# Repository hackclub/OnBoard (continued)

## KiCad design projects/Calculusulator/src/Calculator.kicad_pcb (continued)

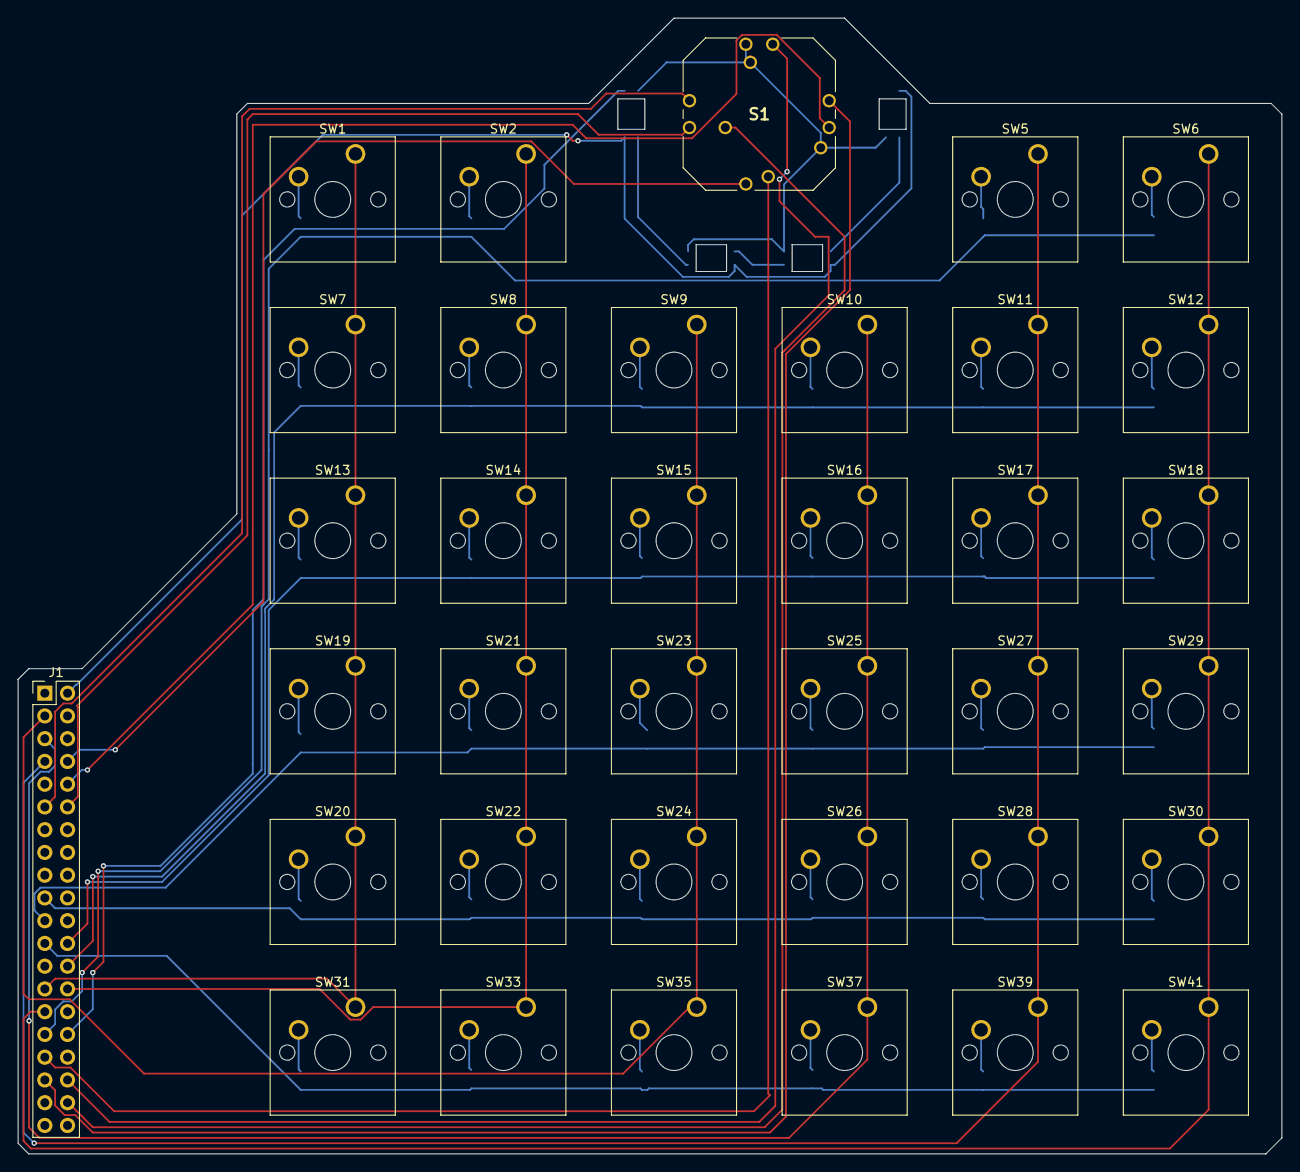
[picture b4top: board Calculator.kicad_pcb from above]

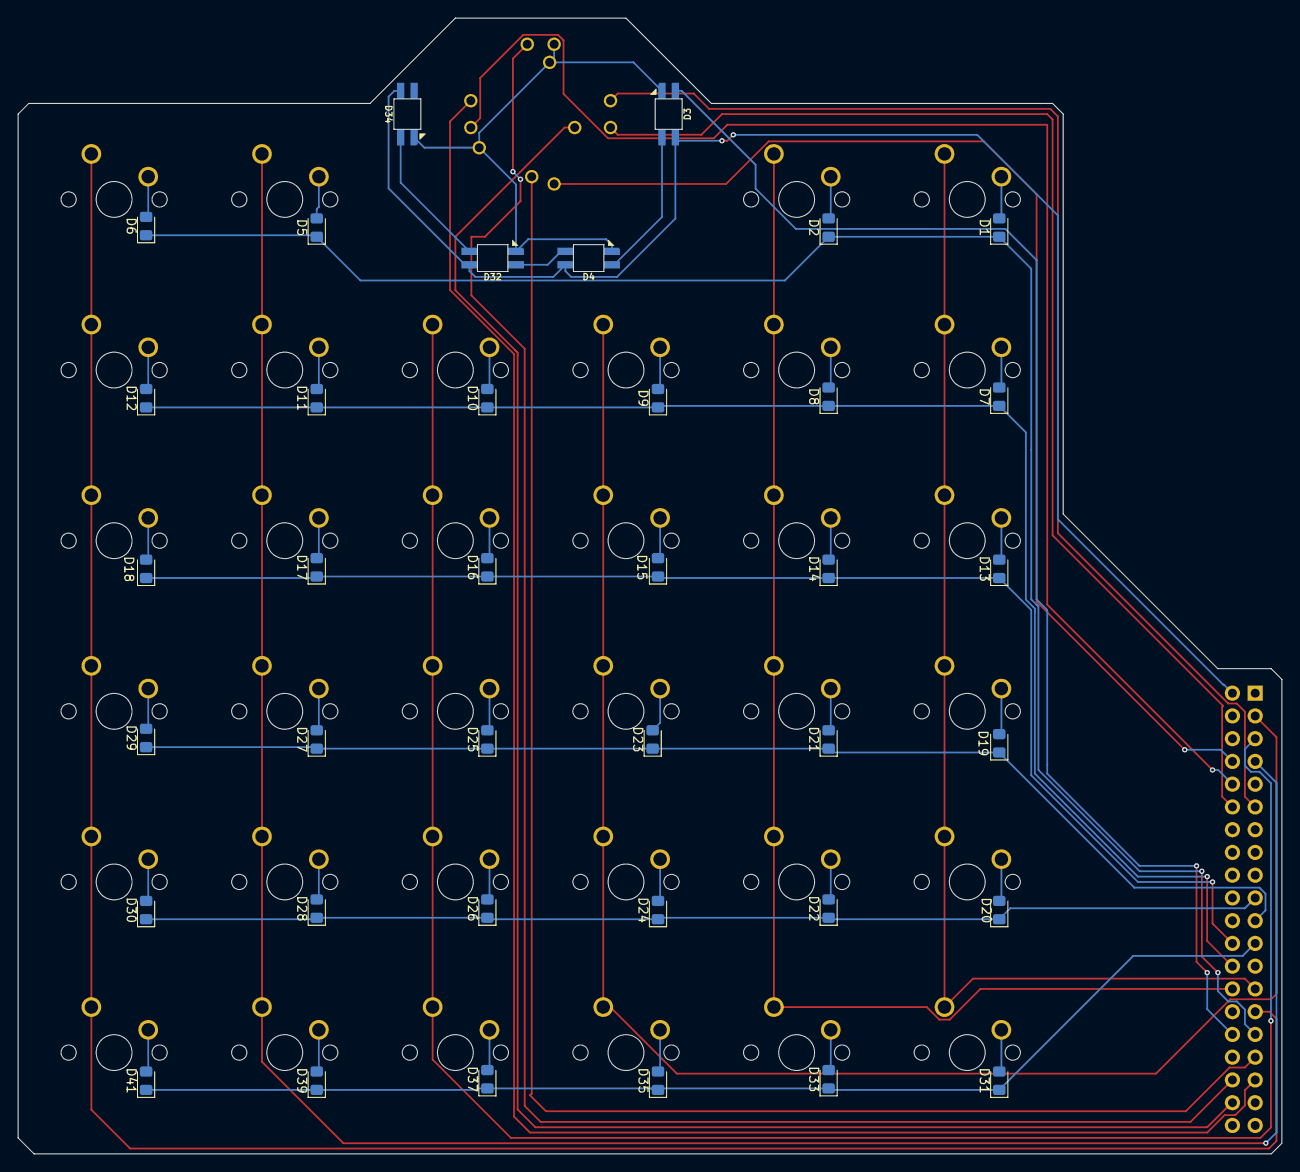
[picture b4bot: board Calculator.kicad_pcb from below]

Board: 2 copper layers, 141.1 x 126.8 mm, 74 parts (38 on the bottom side), 62 nets.

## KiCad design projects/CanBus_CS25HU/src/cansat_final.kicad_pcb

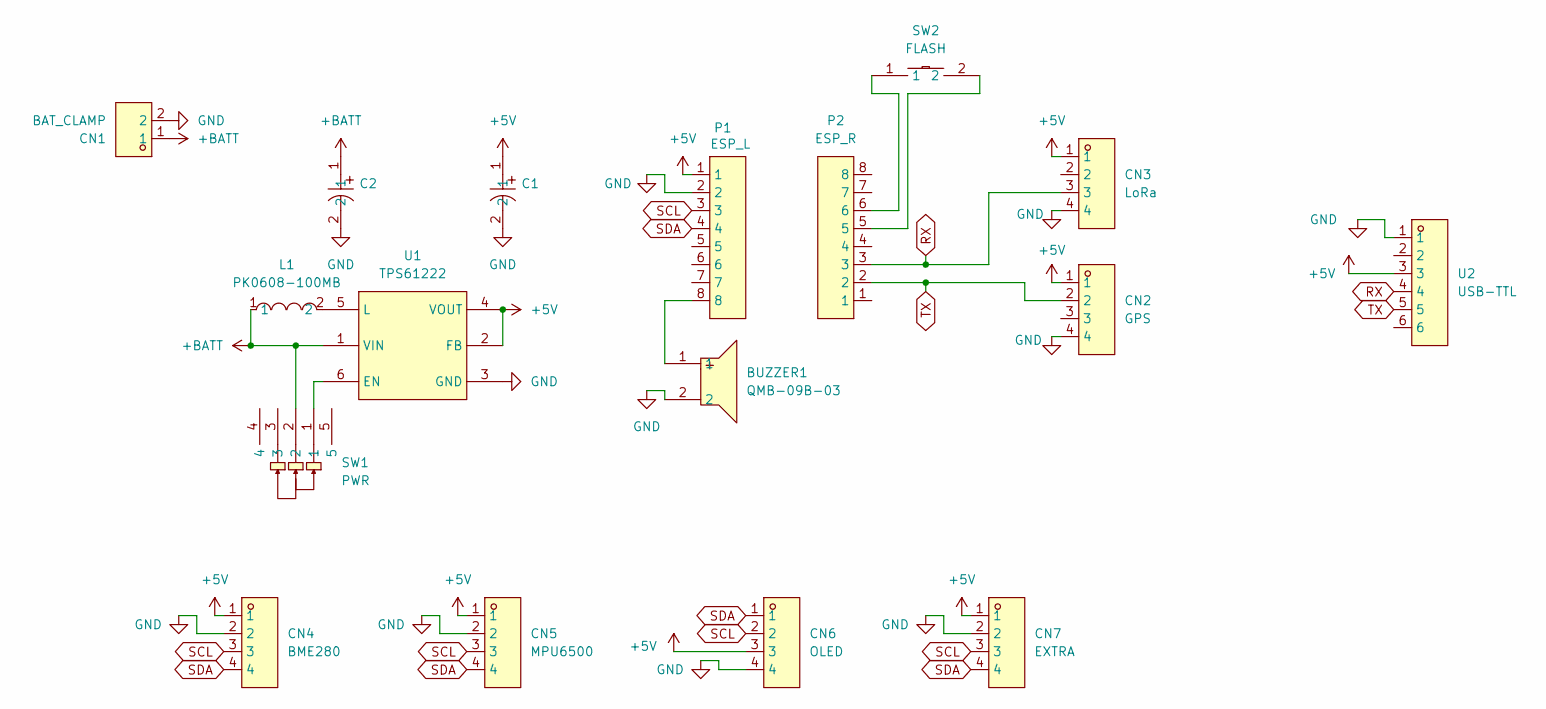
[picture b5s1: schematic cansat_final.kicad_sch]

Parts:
BUZZER1: QMB-09B-03; BUZ-TH_BD9.0-P4.00-D0.6-FD; LCSC Part C96256
C1, C2: 10uF; CAP-TH_BD5.0-P2.00-D0.5-FD-1; LCSC Part C2840034
CN1: BAT_CLAMP; CONN-SMD_2P-P4.00_HDGC4001SMD-S-2P; LCSC Part C5197184
CN2: GPS; CONN-TH_XH-4A; LCSC Part C722867
CN3: LoRa; CONN-TH_XH-4A; LCSC Part C722867
CN4: BME280; CONN-TH_XH-4A; LCSC Part C722867
CN5: MPU6500; CONN-TH_XH-4A; LCSC Part C722867
CN6: OLED; CONN-TH_XH-4A; LCSC Part C722867
CN7: EXTRA; CONN-TH_XH-4A; LCSC Part C722867
L1: PK0608-100MB; IND-TH_BD7.0-P2.50-D0.7; LCSC Part C400296
P1: ESP_L; HDR-TH_8P-P2.54-V-F-1; LCSC Part C27438
P2: ESP_R; HDR-TH_8P-P2.54-V-F-1; LCSC Part C27438
SW1: PWR; SW-TH_SK12D07VG3; LCSC Part C431547
SW2: FLASH; SW-SMD_L6.0-W3.3-LS8.0; LCSC Part C318938
U1: TPS61222; SC-70-6_L2.2-W1.3-P0.65-LS2.1-BR; LCSC Part C116461
U2: USB-TTL; HDR-TH_6P-P2.54-V-F; LCSC Part C7509518

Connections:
+5V: C1.1, CN2.1, CN3.1, CN4.1, CN5.1, CN6.3, CN7.1, P1.1, U1.2 (FB), U1.4 (VOUT), U2.3
+BATT: C2.1, CN1.1, L1.1, SW1.2, U1.1 (VIN)
GND: BUZZER1.2, C1.2, C2.2, CN1.2, CN2.4, CN3.4, CN4.2, CN5.2, CN6.4, CN7.2, P1.2, U1.3 (GND), U2.1
unnamed: BUZZER1.1, P1.8
unnamed: P2.5, SW2.2
unnamed: P2.6, SW2.1
unnamed: SW1.1, U1.6 (EN)
unnamed: L1.2, U1.5 (L)
RX: CN3.3, P2.3, U2.4
SCL: CN4.3, CN5.3, CN6.2, CN7.3, P1.3
SDA: CN4.4, CN5.4, CN6.1, CN7.4, P1.4
TX: CN2.2, P2.2, U2.5

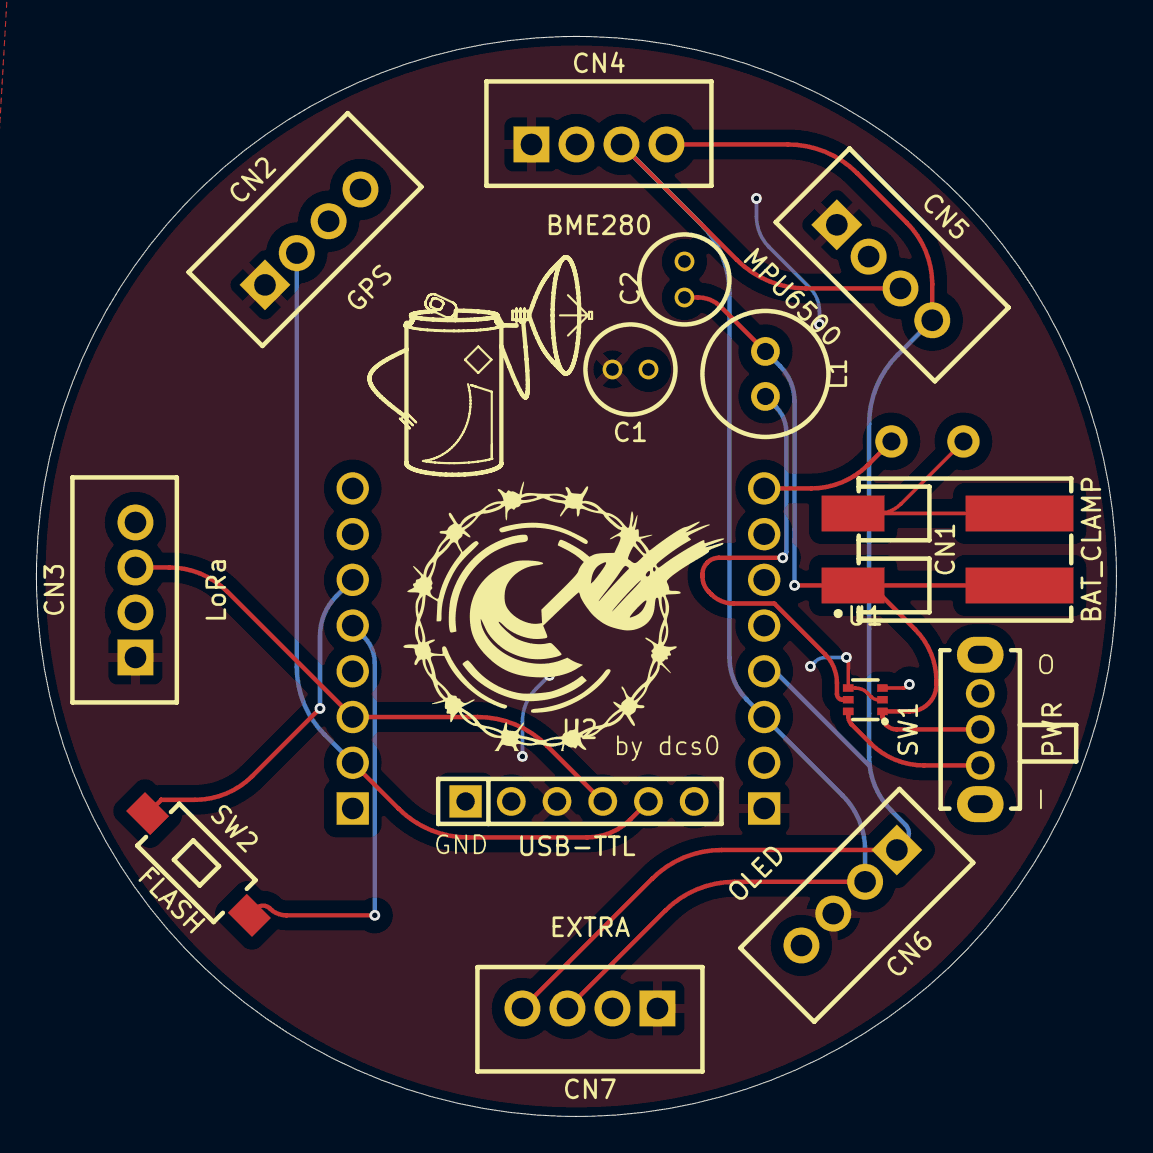
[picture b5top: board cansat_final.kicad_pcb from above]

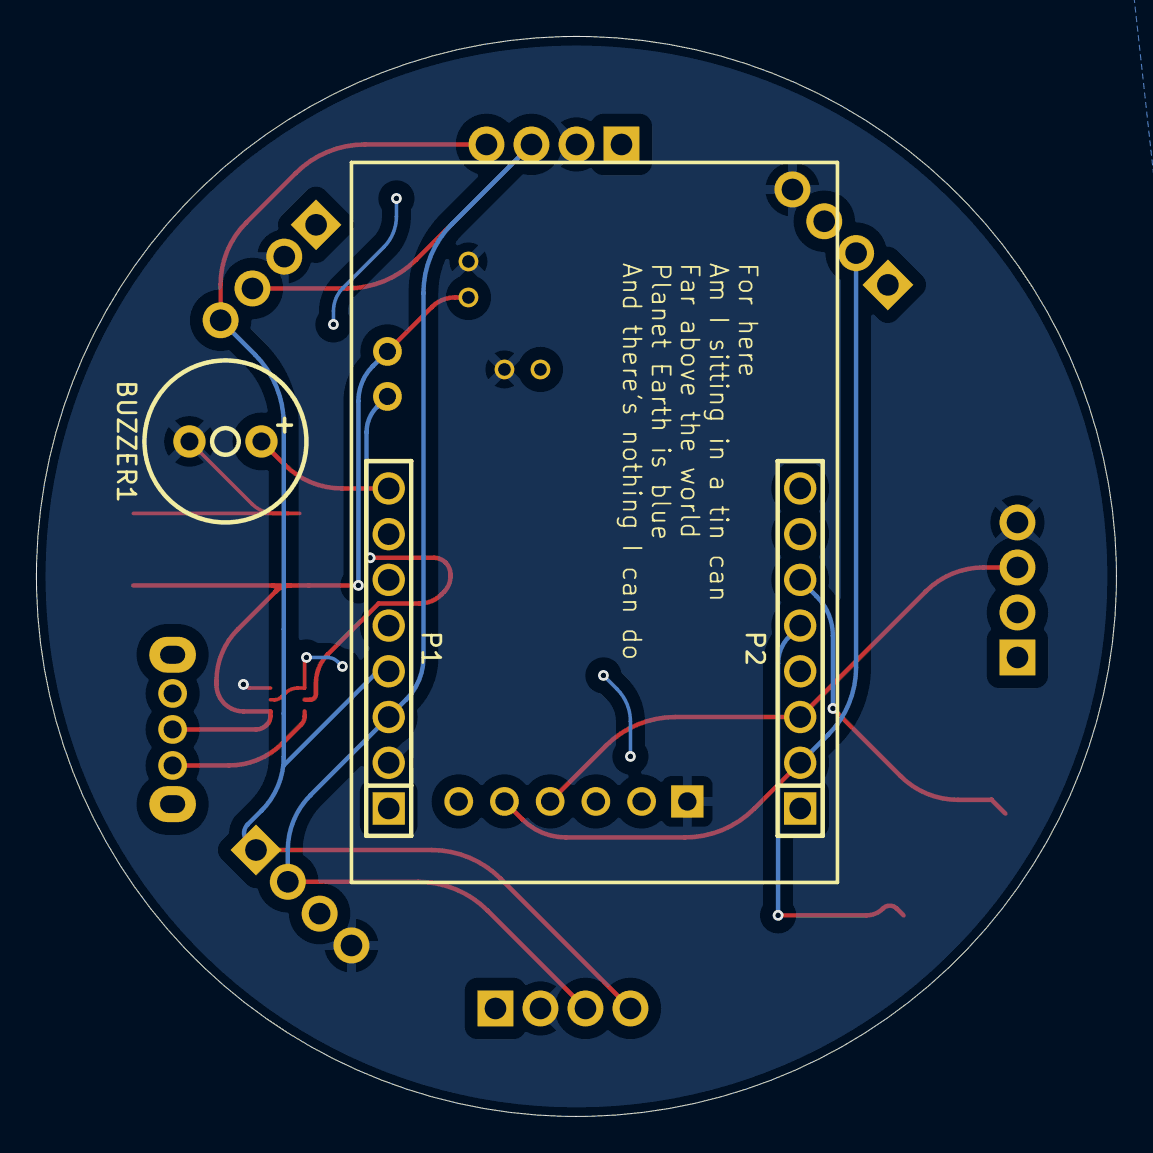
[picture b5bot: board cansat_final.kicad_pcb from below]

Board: 2 copper layers, 60.0 x 60.0 mm, 17 parts (3 on the bottom side), 12 nets.

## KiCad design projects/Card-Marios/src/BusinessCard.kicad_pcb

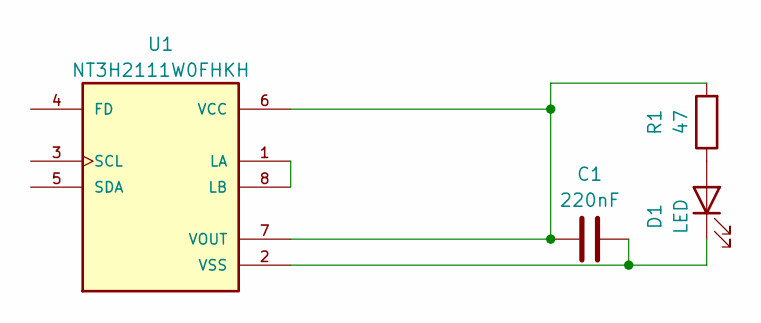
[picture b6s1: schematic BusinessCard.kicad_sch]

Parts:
C1: 220nF; C_0603_1608Metric
D1: LED; LED_0805_2012Metric
R1: 47; R_0603_1608Metric
U1: NT3H2111W0FHKH; QFN8P50_160X160X50L40X20N

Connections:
unnamed: D1.2 (A), R1.1
unnamed: C1.1, D1.1 (K), U1.2 (VSS)
unnamed: U1.1 (LA), U1.8 (LB)
unnamed: C1.2, R1.2, U1.6 (VCC), U1.7 (VOUT)

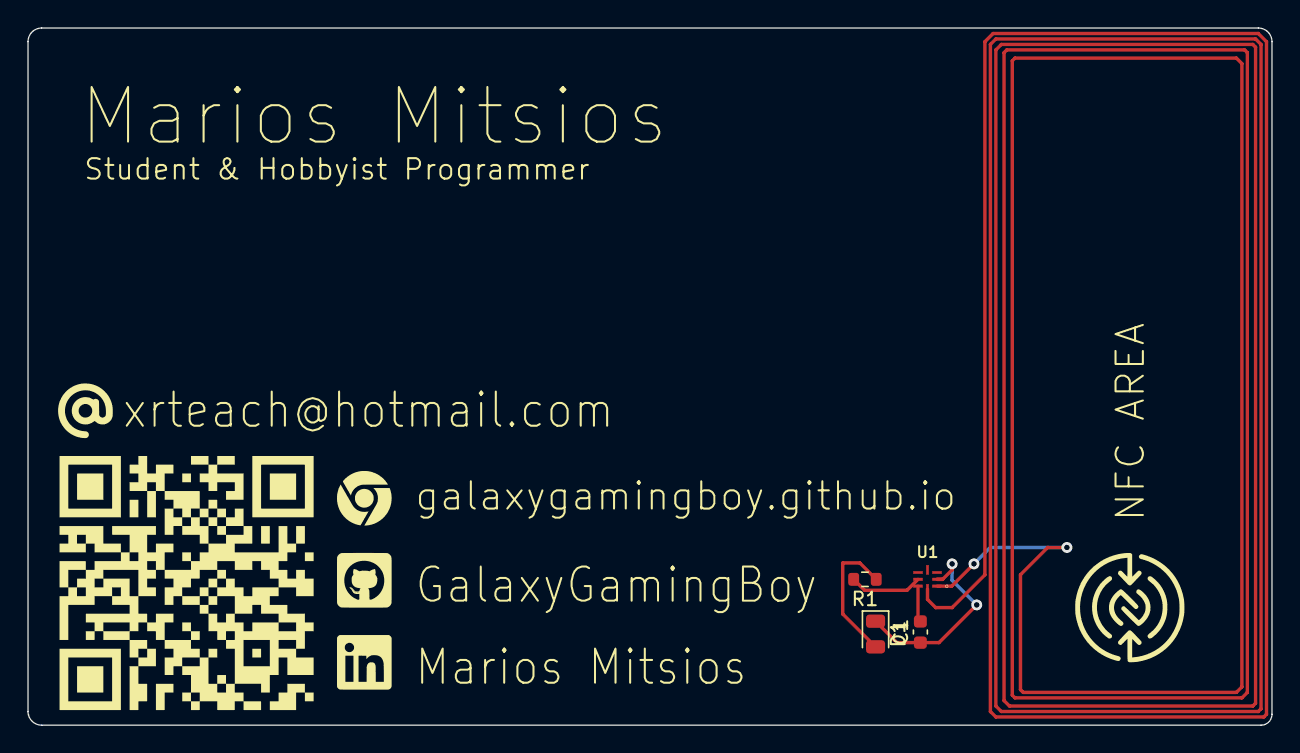
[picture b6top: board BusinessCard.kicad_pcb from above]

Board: 2 copper layers, 91.0 x 51.0 mm, 4 parts (0 on the bottom side), 4 nets.

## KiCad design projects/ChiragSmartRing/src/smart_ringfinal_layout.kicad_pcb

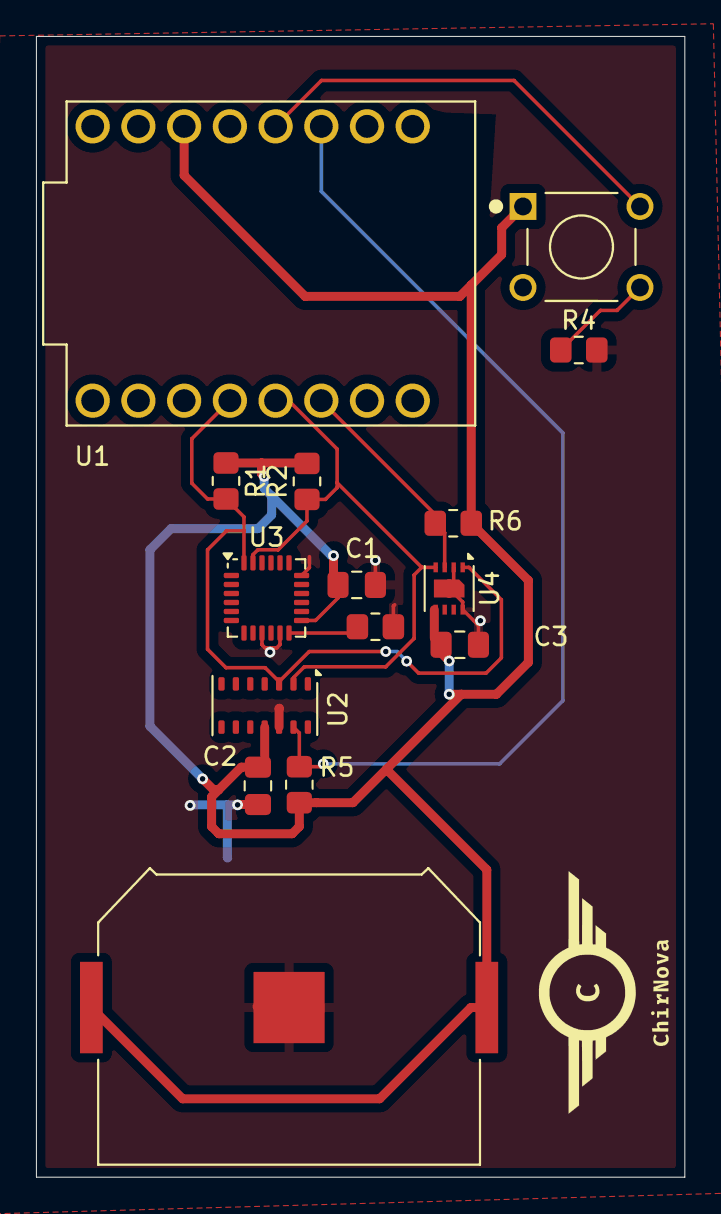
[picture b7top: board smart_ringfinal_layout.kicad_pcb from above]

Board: 2 copper layers, 36.0 x 63.4 mm, 15 parts (0 on the bottom side), 9 nets.

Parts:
BT1: 3034; BAT_3034
C1, C2, C3: 0.1u; C_0805_2012Metric_Pad1.18x1.45mm_HandSolder
R1, R2, R5, R6: 4.7k; R_0805_2012Metric_Pad1.20x1.40mm_HandSolder
R3, R4: 10k; R_0805_2012Metric_Pad1.20x1.40mm_HandSolder
S1: FSM8JH; SW_FSM8JH
U1: ESP32-C3_SUPERMINI_TH; ESP32 C3_MINI
U2: MAX30102; Maxim_OLGA-14_3.3x5.6mm_P0.8mm
U3: MPU-6050; InvenSense_QFN-24_4x4mm_P0.5mm
U4: SHT30-DIS; Sensirion_DFN-8-1EP_2.5x2.5mm_P0.5mm_EP1.1x1.7mm

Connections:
3.3V: BT1.P1, BT1.P2, C1.2, C2.1, C3.2, R1.1, R2.2, R5.2, R6.2, S1.1, U1.3.3 (3V3), U2.11 (VDD), U3.13 (VDD), U4.5 (VDD)
GND: BT1.N, C1.1, C2.2, C3.1, R3.2, R4.2, U2.12 (GND), U3.9 (AD0), U3.11 (FSYNC), U3.18 (GND), U4.2 (ADDR), U4.8 (VSS), U4.9 (VSS)
unnamed: R4.1, S1.4
unnamed: R5.1, U1.2 (GPIO2), U2.13 (~INT)
unnamed: S1.3, U1.3 (GPIO3)
unnamed: R6.1, U1.10 (GPIO10), U4.3 (ALERT)
unnamed: R3.1, U3.12 (INT)
SCL: R2.1, U1.9 (GPIO9), U2.2 (SCL), U3.23 (SCL), U4.4 (SCL)
SDA: R1.2, U1.8 (GPIO8), U2.3 (SDA), U3.24 (SDA), U4.1 (SDA)
